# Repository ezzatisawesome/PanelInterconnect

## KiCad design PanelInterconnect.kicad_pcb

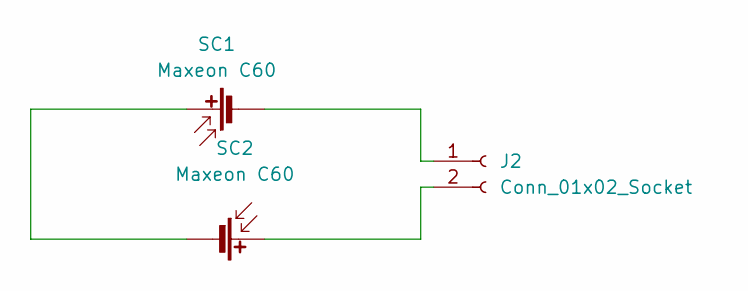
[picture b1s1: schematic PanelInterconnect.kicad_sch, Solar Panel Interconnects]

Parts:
J2: Conn_01x02_Socket; AMASS_XT30U-F_1x02_P5.0mm_Vertical
SC1, SC2: Maxeon C60; maxeon_c60; Mfr P/N C60

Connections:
unnamed: J2.1, SC1.2 (-)
unnamed: J2.2, SC2.1 (+)
unnamed: SC1.1 (+), SC2.2 (-)

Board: 2 copper layers, 3 parts (0 on the bottom side), 3 nets, no tracks yet.

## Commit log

2025-10-25 Starting layout
2025-10-26 Pushing
2025-10-26 Still working on it
2025-10-27 Working on it still
2025-10-29 Cleaning up layout
2025-10-29 Adding finishing touches to PCB and adding fab outputs
2025-11-01 Panelizing interconnects
2025-11-08 Finishing up backup interconnects
2025-11-25 Hello
2025-11-25 Extending
2025-11-25 Adding hirose footprints
2025-11-25 Connection to powerboard
2025-11-25 Shifitng to single connection
2026-03-04 updated panel interconnect
2026-03-04 update Panel Interconnects
